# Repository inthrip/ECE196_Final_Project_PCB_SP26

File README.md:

# ECE196_Final_Project_PCB_SP26

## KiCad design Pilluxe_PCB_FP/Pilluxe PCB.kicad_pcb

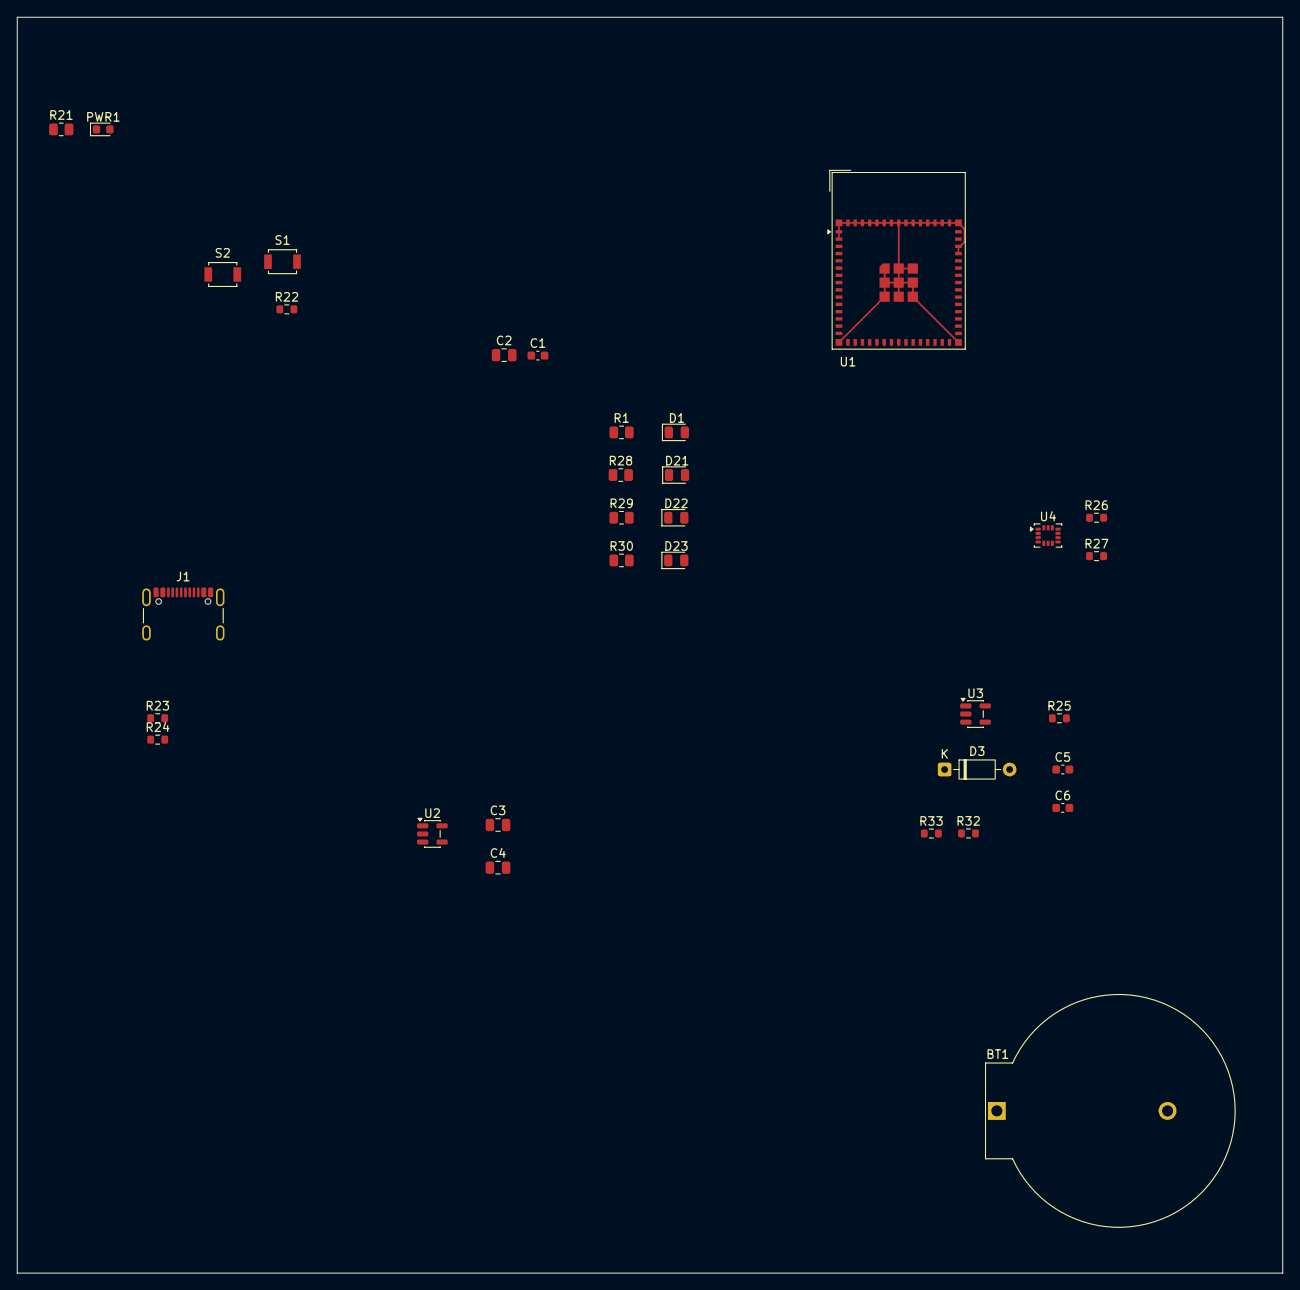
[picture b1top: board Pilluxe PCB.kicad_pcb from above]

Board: 2 copper layers, 148.3 x 147.1 mm, 33 parts (0 on the bottom side), 17 nets.

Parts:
BT1: Battery; BatteryHolder_ComfortableElectronic_CH273-2450_1x2450
C1: .1uF; C_0603_1608Metric
C2, C3, C4: 10uF; C_0805_2012Metric
C5, C6: 4.7uF; C_0603_1608Metric
D1, D21, D22, D23: LED; LED_0805_2012Metric
D3: 1N914; D_DO-35_SOD27_P7.62mm_Horizontal
J1: USB_C_Receptacle_USB2.0_16P; USB_C_Receptacle_GCT_USB4105-xx-A_16P_TopMnt_Horizontal
PWR1: LED; LED_0603_1608Metric
R1, R28, R29, R30: 1000; R_0805_2012Metric
R21: 1k; R_0805_2012Metric
R22, R25: 10k; R_0603_1608Metric
R23, R24: 5.1k; R_0603_1608Metric
R26, R27: 4.7k; R_0603_1608Metric
R32, R33: 100k; R_0603_1608Metric
S1: RESETSW; SW_SPST_B3U-1000P
S2: BOOTSW; SW_SPST_B3U-1000P
U1: ESP32-S3-MINI-1; ESP32-S2-MINI-1
U2: AP2112K-3.3; SOT-23-5
U3: MCP73831-2-OT; SOT-23-5
U4: LSM6DSL; LGA-14_3x2.5mm_P0.5mm_LayoutBorder3x4y

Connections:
+3.3V: C1.1, C2.1, C4.1, R21.1, R22.1, R26.1, R27.2, U1.3 (3V3), U2.5 (VOUT), U4.5 (VDDIO), U4.8 (VDD)
+5V: C3.1, C5.2, J1.A4 (VBUS), J1.A9 (VBUS), J1.B4 (VBUS), J1.B9 (VBUS), U2.1 (VIN), U2.3 (EN), U3.4 (V_{DD})
/BOOT: S2.1, U1.4 (IO0)
/D+: J1.A6 (D+), J1.B6 (D+), U1.24 (USB_D+)
/D-: J1.A7 (D-), J1.B7 (D-), U1.23 (USB_D-)
/RESET: R22.2, S1.1, U1.45 (EN)
GND: BT1.2 (-), C1.2, C2.2, C3.2, C4.2, C5.1, C6.2, J1.A1 (GND), J1.A12 (GND), J1.B1 (GND), J1.B12 (GND), PWR1.1 (K), R1.2, R23.2, R24.2, R25.2, R28.2, R29.2, R30.2, R32.1, S1.2, S2.2, U1.1 (GND), U1.2 (GND), U1.42 (GND), U1.43 (GND), U1.46 (GND), U1.47 (GND), U1.48 (GND), U1.49 (GND), U1.50 (GND), U1.51 (GND), U1.52 (GND), U1.53 (GND), U1.54 (GND), U1.55 (GND), U1.56 (GND), U1.57 (GND), U1.58 (GND), U1.59 (GND), U1.60 (GND), U1.61 (GND), U1.62 (GND), U1.63 (GND), U1.64 (GND), U1.65 (GND), U2.2 (GND), U3.2 (V_{SS}), U4.1 (SDO/SA0), U4.6 (GND), U4.7 (GND)
unnamed: BT1.1 (+), D3.2 (A)
unnamed: D1.1 (K_1), R1.1
unnamed: C6.1, D3.1 (K), R33.2, U3.3 (V_{BAT})
unnamed: D21.1 (K_1), R28.1
unnamed: D22.1 (K_1), R29.1
unnamed: D23.1 (K_1), R30.1
unnamed: J1.A5 (CC1), R23.1
unnamed: J1.B5 (CC2), R24.1
unnamed: PWR1.2 (A), R21.2
unnamed: R25.1, U3.5 (PROG)

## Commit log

2026-04-24 Add content to remove.md
2026-04-24 Ignore local history folder
2026-04-27 Adding battery to the schematic attached to NOTHING
2026-04-28 adding capacitor
